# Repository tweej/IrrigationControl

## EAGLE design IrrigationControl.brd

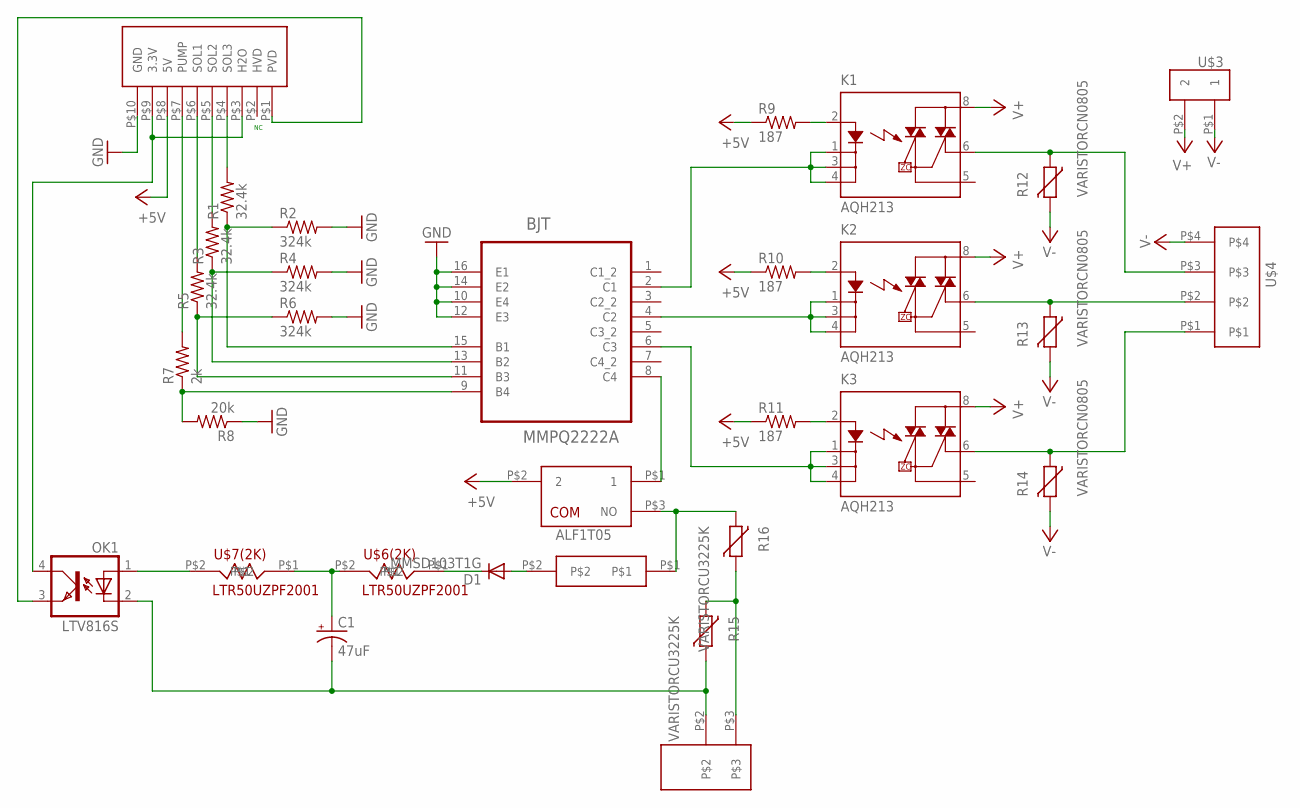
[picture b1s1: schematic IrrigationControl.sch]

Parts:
ALF1T05: ALF1T05; TMP
BJT: MMPQ2222A; SOIC127P600X175-16N
C1: 47uF; E5-10,5
D1: MMSD103T1G; SOD123
K1, K2, K3: AQH213; DIL07
OK1: LTV816S; SMD4
R1, R3, R5: 32.4k; R0805
R2, R4, R6: 324k; R0805
R7: 2k; R0805
R8: 20k; R0805
R9, R10, R11: 187; R0805
R12, R13, R14: VARISTORCN0805; CT/CN0805
R15, R16: VARISTORCU3225K; CU3225K
U$1: OSTT7030150
U$2: OSTTE100104
U$3: OSTTC020162
U$4: OSTTE040104; OSTTEX040104
U$5: SST-357; SST
U$6(2K), U$7(2K): LTR50UZPF2001; WIDE2010

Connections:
+5V: ALF1T05.P$2 (2), R9.1, R10.1, R11.1, U$2.P$8 (5V)
GND: BJT.10 (E4), BJT.12 (E3), BJT.14 (E2), BJT.16 (E1), R2.2, R4.2, R6.2, R8.1, U$2.P$10 (GND)
unnamed: BJT.13 (B2), R3.1, R4.1
unnamed: R7.2, U$2.P$7 (PUMP)
unnamed: BJT.15 (B1), R1.1, R2.1
unnamed: R5.2, U$2.P$6 (SOL1)
unnamed: R3.2, U$2.P$5 (SOL2)
unnamed: BJT.11 (B3), R5.1, R6.1
unnamed: BJT.9 (B4), R7.1, R8.2
unnamed: OK1.4 (COL), U$2.P$3 (H2O), U$2.P$9 (3.3V)
unnamed: ALF1T05.P$1 (1), BJT.8 (C4)
unnamed: ALF1T05.P$3 (NO), R16.2, U$5.P$1
unnamed: K3.2 (A), R11.2
unnamed: K2.2 (A), R10.2
unnamed: K1.2 (A), R9.2
unnamed: BJT.6 (C3), K3.1 (K), K3.3 (K1), K3.4 (K2)
unnamed: BJT.4 (C2), K2.1 (K), K2.3 (K1), K2.4 (K2)
unnamed: BJT.2 (C1), K1.1 (K), K1.3 (K1), K1.4 (K2)
unnamed: K1.6 (DS3), R12.1, U$4.P$3
unnamed: K2.6 (DS3), R13.1, U$4.P$2
unnamed: K3.6 (DS3), R14.1, U$4.P$1
unnamed: D1.A, U$5.P$2
unnamed: R15.2, R16.1, U$1.P$3
unnamed: C1.-, OK1.2 (C), R15.1, U$1.P$2
unnamed: D1.C, U$6(2K).P$1
unnamed: C1.+, U$6(2K).P$2, U$7(2K).P$1
unnamed: OK1.1 (A), U$7(2K).P$2
unnamed: OK1.3 (EMIT), U$2.P$1 (PVD)
unnamed: R1.2, U$2.P$4 (SOL3)
V+: K1.8 (DS1), K2.8 (DS1), K3.8 (DS1), U$3.P$2 (2)
V-: R12.2, R13.2, R14.2, U$3.P$1 (1), U$4.P$4

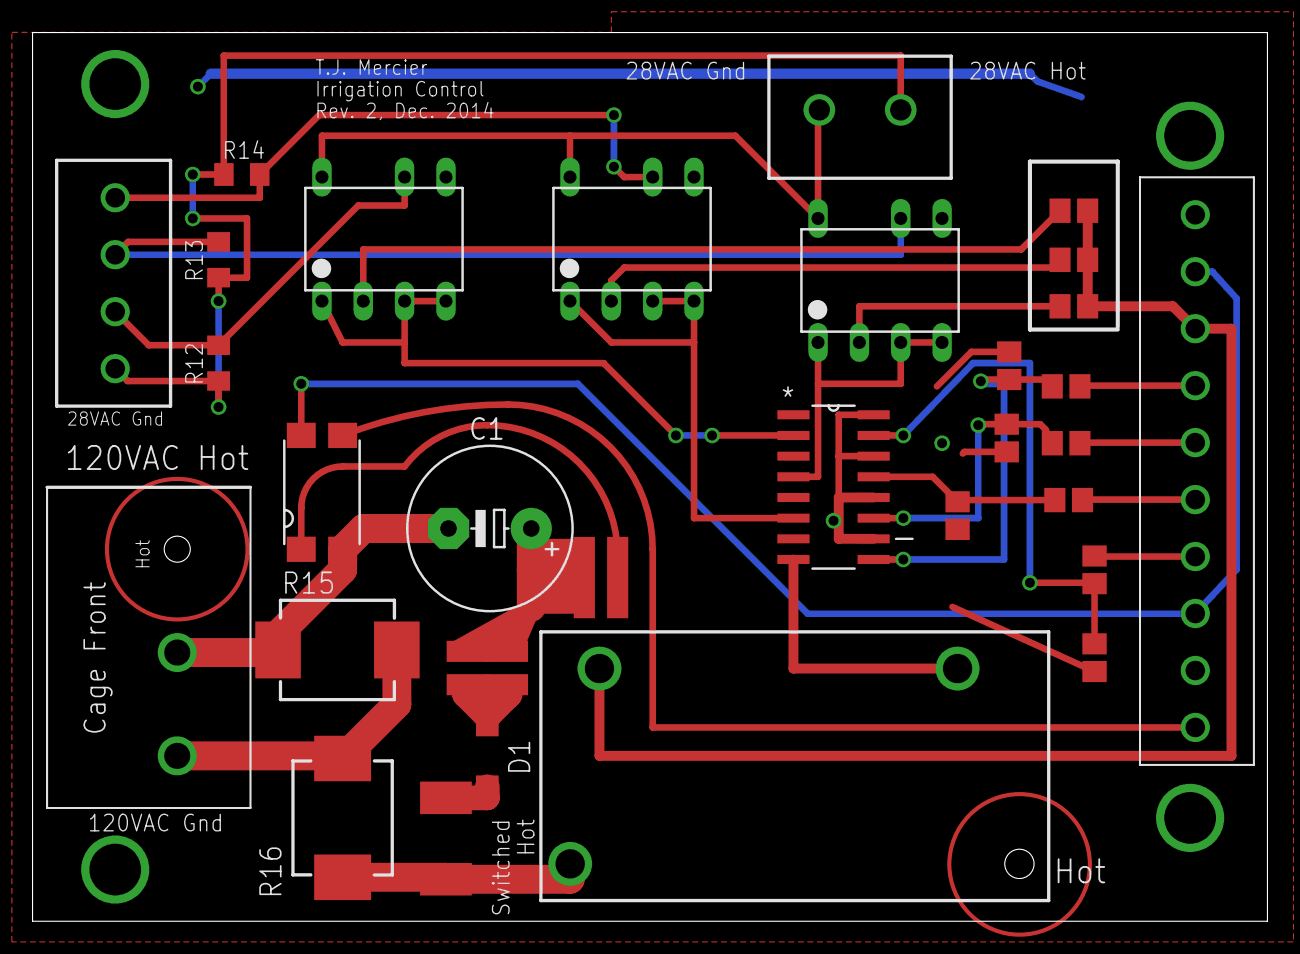
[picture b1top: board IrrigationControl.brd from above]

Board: 2 copper layers, 75.9 x 54.6 mm, 31 parts (0 on the bottom side), 31 nets.

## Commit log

2015-01-13 Schematic, Board Layout, Gerbers Also included necessary TJ library, as well as Jeremy Blum's CAM processor configuration
2016-07-10 Include name in LICENSE
